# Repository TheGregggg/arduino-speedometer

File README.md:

# Arduino Speedometer
This is a speedometer for sim racing, built using an Arduino, a servo motor and a four-digit, eight-segment display.  

This speedometer displays analogue engine RPM via the servo motor and digital speed in km/h via the four-digit LED display.  

The server is programmed in C and currently support only Forza Horizon 4.
The game is configured to send data packets to the server. The server parses the packet and only uses the RPM and speed and send it to the Arduino via UART in a special byte format that compresses the RPM and the speed into 3 bytes.

## Planned improvements
- Update it to support other games, such as Forza Horizon 5 (not tested but should be straightforward) and Assetto Corsa (specific logic needs to be done for this game).  
- Improve visuals with a white dial across all the half circle.  
- Paint the needle red to make it more visible.  

# Build
I wanted to build something modular, reparable and with off the shelf components, specifically what I have lying around.

That's why I used an Arduino UNO as the microcontroller.
I also used a 3461BS as the 4 digits 8 segments display paired with a HC595 8 bit shift register.

The first prototype was realised with a breadboard and cardboard.

*First prototype with all the components mounted on a breadboard and the servo attached to a cardboard dial*

I then created a custom board for all the components.
All the resistors, the DIP socket for the HC595 and a decoupling capacitor for the servo motor were mounted and soldered on a stripboard for a clean finished product.

*Hand soldered stripboard :) you don't want to look to the other way.*

Pins were also soldered to facilitate connections between this board and the Arduino and the 3461BS.

The custom board was tested with everything plugged in.

*Prototype cardboard speedometer using the stripboard*

I designed the shell in FreeCAD to learn 3D modelling and then 3D printed it in PLA.
I then assembled everything into a tiny and neat product.

*Fitting all components together in the tight shell. Threaded inserts were used to facilitate screw mounting of the components and to allow disassembly!*

# Work Reference
STEP files used as 3D reference for case design:  
- https://www.printables.com/model/360145-micro-servo-3d-model-stp/files
- https://www.printables.com/model/358867-arduino-uno-3d-model-stp/files

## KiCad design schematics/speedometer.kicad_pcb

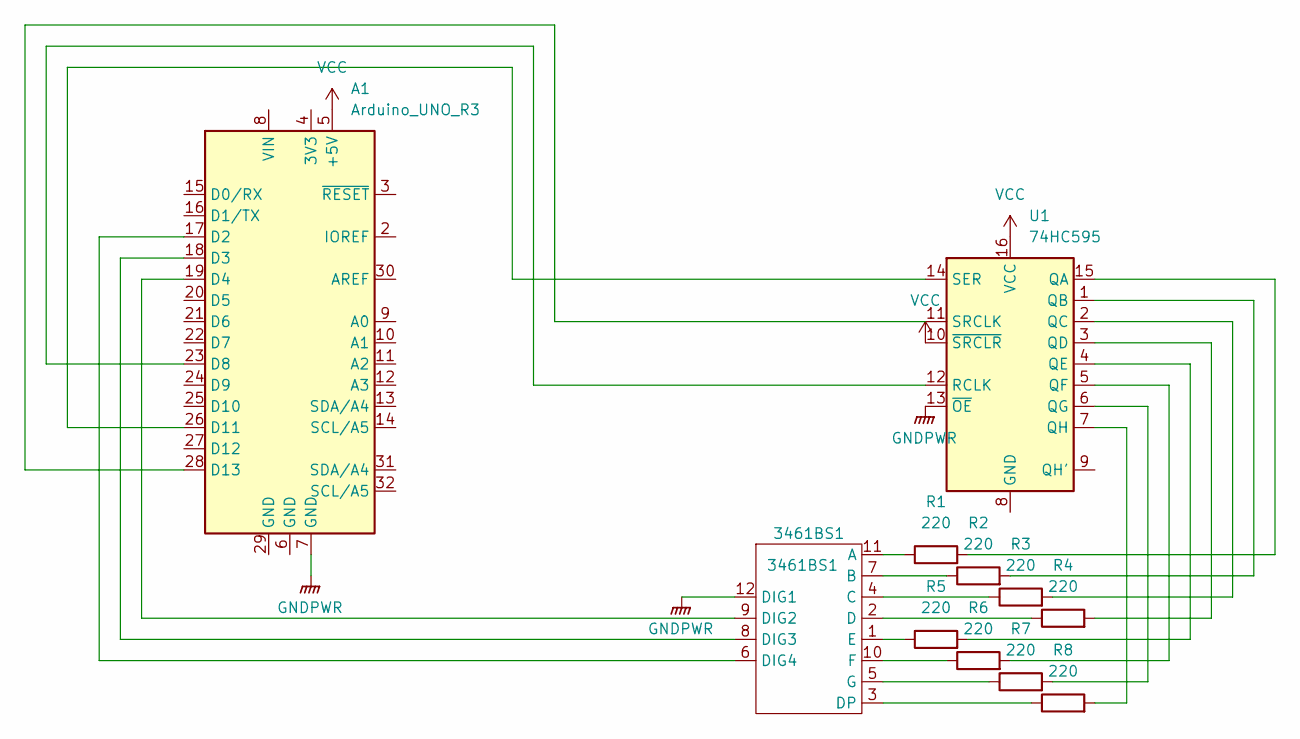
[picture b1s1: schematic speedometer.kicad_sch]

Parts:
3461BS1: 3461BS1; DIP-12_W7.62mm
A1: Arduino_UNO_R3
R1, R2, R3, R4, R5, R6, R7, R8: 220; R_Axial_DIN0204_L3.6mm_D1.6mm_P1.90mm_Vertical
U1: 74HC595; CERDIP-16_W7.62mm_SideBrazed

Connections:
GNDPWR: 3461BS1.12 (DIG1), A1.7 (GND), U1.13 (~OE)
unnamed: 3461BS1.11 (A), R1.1
unnamed: 3461BS1.7 (B), R2.1
unnamed: 3461BS1.4 (C), R3.1
unnamed: 3461BS1.2 (D), R4.1
unnamed: 3461BS1.9 (DIG2), A1.19 (D4)
unnamed: 3461BS1.8 (DIG3), A1.18 (D3)
unnamed: 3461BS1.6 (DIG4), A1.17 (D2)
unnamed: 3461BS1.3 (DP), R8.1
unnamed: 3461BS1.1 (E), R5.1
unnamed: 3461BS1.10 (F), R6.1
unnamed: 3461BS1.5 (G), R7.1
unnamed: A1.23 (D8), U1.12 (RCLK)
unnamed: A1.26 (D11), U1.14 (SER)
unnamed: A1.28 (D13), U1.11 (SRCLK)
unnamed: R1.2, U1.15 (QA)
unnamed: R2.2, U1.1 (QB)
unnamed: R3.2, U1.2 (QC)
unnamed: R4.2, U1.3 (QD)
unnamed: R5.2, U1.4 (QE)
unnamed: R6.2, U1.5 (QF)
unnamed: R7.2, U1.6 (QG)
unnamed: R8.2, U1.7 (QH)
VCC: A1.5 (+5V), U1.10 (~SRCLR), U1.16 (VCC)

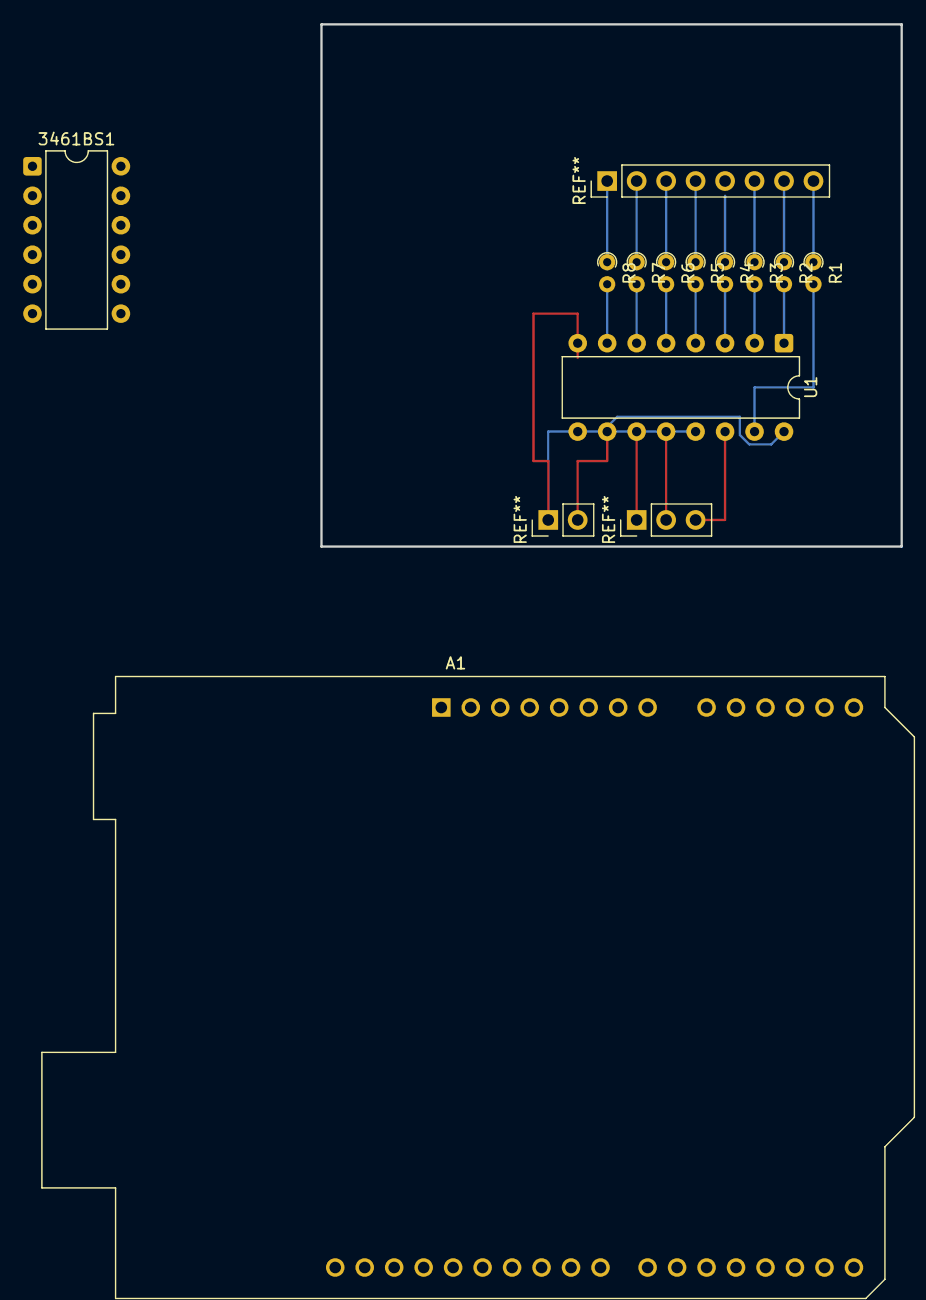
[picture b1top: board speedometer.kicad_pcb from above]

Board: 2 copper layers, 50.0 x 45.0 mm, 11 parts (0 on the bottom side), 24 nets.

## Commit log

2025-05-08 arduino code and python begin
2025-05-08 python code retrieving forza data
2025-05-17 adding datasheets
2025-05-17 beter nix shell and small make file to build and upload
2025-05-17 adding code to show vehicule speed onto 4 digits 8 segments display
2025-05-17 add ATmega328P datasheet
2025-05-18 udp server in c
2025-05-18 update python code
2025-05-18 update gitignore
2025-05-18 speedometer + rpm working
2025-05-22 CAD shell first draft
2025-05-29 update 3d model
2025-07-06 new version of 3d model ongoing
2025-12-15 add cad files
2025-12-15 add schematics files in KiCAD
2025-12-15 add common anode LED datasheet
2025-12-15 fixe for final assembly with anode led 4 digit
2025-12-15 add a beginning readme explaining this cool project
2026-06-14 refactored to use defined offset macro
2026-06-14 removed old python app and trash
2026-06-14 renamed server to main, started working on thread and tui feedback
